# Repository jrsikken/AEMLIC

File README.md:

The AEMLIC is a 15x20mm board with the AEM10941 Solar Harvesting IC from E-peas. It efficiently converts solar panel energy into LIC charge, it even works with indoor light. It has one regulated output that is enabled when the LIC has sufficient charge, and a low voltage warning that informs the user of impending shutdown when the LIC runs low. It easily integrates in other projects because of the castellated via's, and when soldered onto 0.1' pitch headers it fits in a bread board.

The .xlsx contains the AEMLIC PCB specification, Bill of Materials, the placement drawing, and the XY positions file 
The .zip files contains the PCB gerber files
The .sch and .pcb are Eagle Design files

I am selling this board here:
https://www.tindie.com/products/jaspersikken/solar-harvesting-into-lithium-ion-capacitor/

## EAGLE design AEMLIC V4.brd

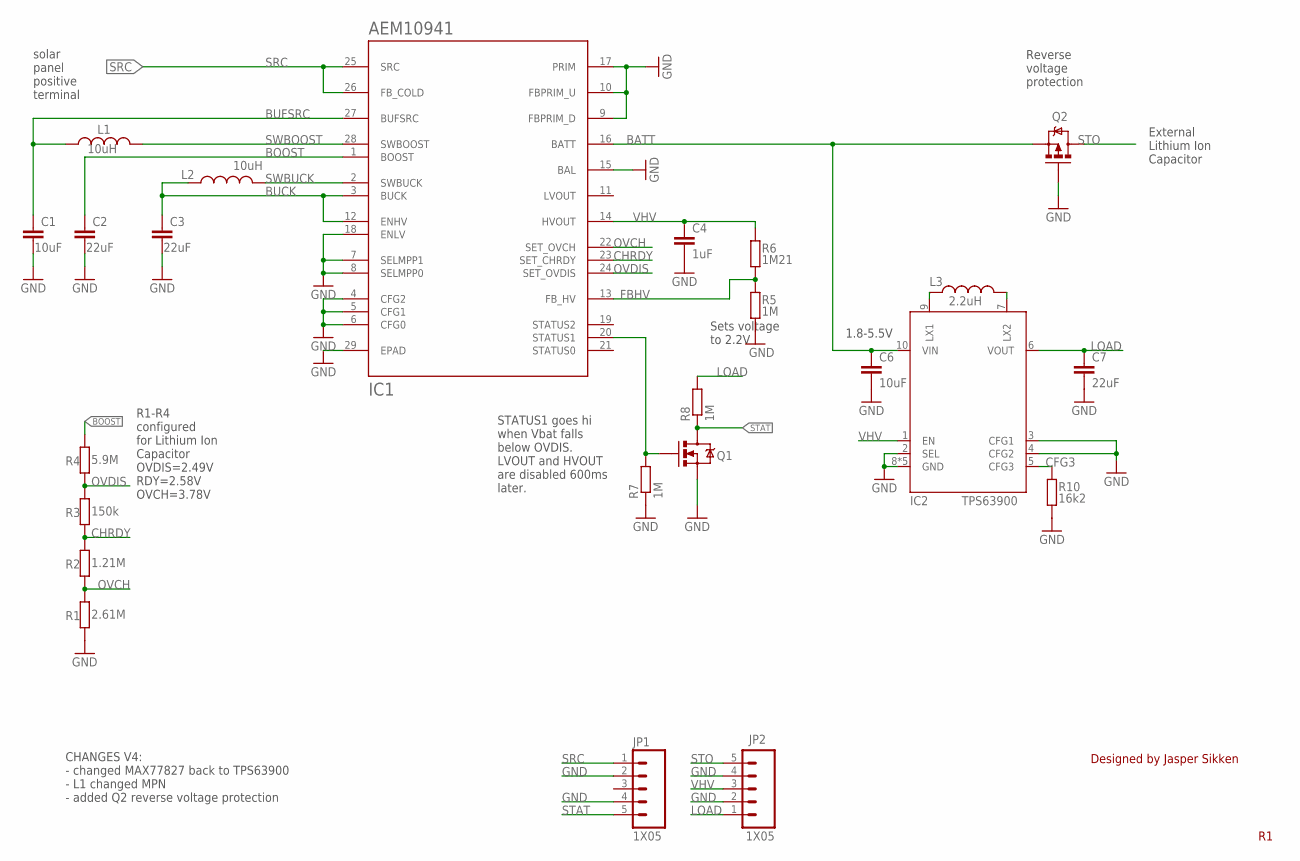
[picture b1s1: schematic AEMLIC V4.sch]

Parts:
C1: 10uF; C0603; MPN 1049P
C2: 22uF; C0603; MPN CGA5L1X7S1A226M160AC
C3: 22uF; C0603; MPN 1049P
C4: 1uF; C0603
C6: 10uF; C0603
C7: 22uF; C0603
IC1: AEM10941; QFN50P505X505X90-28
IC2: TPS63900; WSON10
JP1, JP2: 1X05; 1X05_2.54MM_ROUND_NOSILK
L1: 10uH; L_3225MM
L2: 10uH; L0603; MPN CK2125100M-T
L3: 2.2uH; L_1008_[2520]
Q1: DMG1012UW; SOT323
Q2: DMP2160UW; SOT323
R1: 2.61M; R0402
R2: 1.21M; R0402
R3: 150k; R0402
R4: 5.9M; R0402
R5, R7, R8: 1M; R0402
R6: 1M21; R0402
R10: 16k2; R0402

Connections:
BATT: C6.1, IC1.16 (BATT), IC2.10 (VIN), Q2.2 (S)
BOOST: C2.1, IC1.1 (BOOST), R4.2
BUCK: C3.1, IC1.3 (BUCK), IC1.12 (ENHV), L2.1
BUFSRC: C1.1, IC1.27 (BUFSRC), L1.1
CFG3: IC2.5 (CFG3), R10.1
CHRDY: IC1.23 (SET_CHRDY), R2.2, R3.1
FBHV: IC1.13 (FB_HV), R5.2, R6.1
GND: C1.2, C2.2, C3.2, C4.2, C6.2, C7.2, IC1.4 (CFG2), IC1.5 (CFG1), IC1.6 (CFG0), IC1.7 (SELMPP1), IC1.8 (SELMPP0), IC1.9 (FBPRIM_D), IC1.10 (FBPRIM_U), IC1.15 (BAL), IC1.17 (PRIM), IC1.18 (ENLV), IC1.29 (EPAD), IC2.2 (SEL), IC2.3 (CFG1), IC2.4 (CFG2), IC2.8 (GND), IC2.29 (GND), IC2.P$2 (GND), IC2.P$4 (GND), IC2.P$5 (GND), JP1.2, JP1.4, JP2.2, JP2.4, Q1.2 (S), Q2.1 (G), R1.1, R5.1, R7.1, R10.2
LOAD: C7.1, IC2.6 (VOUT), JP2.1, R8.2
unnamed: IC2.9 (LX1), L3.1
unnamed: IC2.7 (LX2), L3.2
OVCH: IC1.22 (SET_OVCH), R1.2, R2.1
OVDIS: IC1.24 (SET_OVDIS), R3.2, R4.1
SRC: IC1.25 (SRC), IC1.26 (FB_COLD), JP1.1
STAT: JP1.5, Q1.3 (D), R8.1
STATUS1: IC1.20 (STATUS1), Q1.1 (G), R7.2
STO: JP2.5, Q2.3 (D)
SWBOOST: IC1.28 (SWBOOST), L1.2
SWBUCK: IC1.2 (SWBUCK), L2.2
VHV: C4.1, IC1.14 (HVOUT), IC2.1 (EN), JP2.3, R6.2

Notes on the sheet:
Designed by Jasper Sikken
solar panel positive terminal
1.8-5.5V
STATUS1 goes hi when Vbat falls below OVDIS. LVOUT and HVOUT are disabled 600ms later.
Sets voltage to 2.2V
R1-R4 configured for Lithium Ion Capacitor OVDIS=2.49V RDY=2.58V OVCH=3.78V
External Lithium Ion Capacitor
Reverse voltage protection
CHANGES V4: - changed MAX77827 back to TPS63900 - L1 changed MPN - added Q2 reverse voltage protection

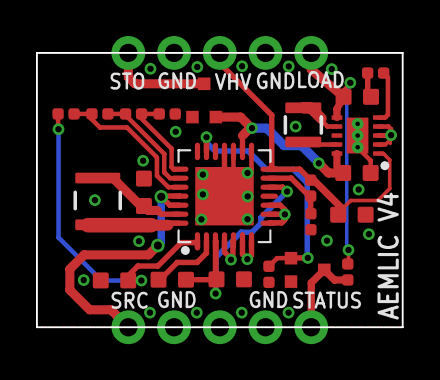
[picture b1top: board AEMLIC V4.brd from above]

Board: 2 copper layers, 20.3 x 15.2 mm, 24 parts (0 on the bottom side), 20 nets.

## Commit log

2021-05-22 Add files via upload
    PCB specification, Bill of Materials, placement drawing and XY positions file
2021-05-22 Add files via upload
    AEMLIC V1 Gerber files
2021-05-22 Add files via upload
    AEMLIC eagle design files
